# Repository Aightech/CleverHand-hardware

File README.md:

# CleverHand — Hardware

This repository contains the **hardware implementation** of the CleverHand platform.

CleverHand is an open-source, modular **Human–Machine Interface (HMI) platform** designed for
research, education, and rapid prototyping in neurotechnology, robotics, and human–robot interaction.

The hardware repository provides:

* modular PCB designs (KiCad),
* mechanical integration assets,
* manufacturing outputs,
* and per-module documentation and quality metadata.

> This repository focuses **only on hardware**.
> Firmware, software, tools, and platform-level documentation live in sibling repositories.

---

## Position in the CleverHand platform

CleverHand is structured as a **hardware / firmware / software stack**:

* **Hardware** (this repo)
  Modular, chainable PCBs for sensing, actuation, and interfacing with the human body.

* **Firmware**
  Low-level drivers, bus control, synchronization, and data transport.

* **Software & SDKs**
  Host interfaces (GUI, Python, C++, LSL, ROS, etc.).

This separation allows:

* independent evolution of hardware and software,
* reproducible research setups,
* and multiple integration paths (DIY, PCBA, pre-assembled).

---

## Intended use & scope

CleverHand hardware is designed for:

* research experiments,
* educational use,
* prototyping of assistive and interactive systems.

It is **not**:

* a medical device,
* a certified clinical system,
* a consumer product.

All designs are provided **as-is**, with readiness and quality explicitly documented per module.

---

## Design goals & constraints

| Constraint          | Status | Notes                        |
| ------------------- | :----: | ---------------------------- |
| Wearable            |   ⚒️   | Wireless support in progress |
| ≥16 channels        |    ✅   | Up to 256 channels (32 × 8)  |
| ≥2 kHz bandwidth    |    ✅   | Up to 2.5 kHz                |
| ≥16-bit resolution  |    ✅   | Up to 24-bit                 |
| Bipolar / monopolar |    ✅   | Module-dependent             |
| Modular             |    ✅   | 1–32 modules per bus         |
| Affordable          |    ✅   | ~£10–£30 per module          |
| Open-source         |    ✅   | Hardware, firmware, software |

---

## Hardware architecture overview

The hardware platform is built around a **chainable modular architecture**.

Each CleverHand system is composed of:

* a **controller** (host interface and timing),
* one **communication module** (bus arbitration),
* one or more **HMI modules**, assembled from submodules.

### Submodule types

HMI nodes are built by stacking standardized submodules:

* **Communication submodule**
  Address decoding, bus routing, chip-select handling.

* **Sensor submodule**
  Biosignal or motion acquisition (EMG, IMU, etc.).

* **Feedback submodule**
  User feedback (vibration, electrotactile stimulation, LEDs).

* **Interface submodule**
  Physical interface to the body (dry electrodes, jack, flex PCB).

This structure allows:

* rapid reconfiguration,
* high channel density,
* reuse of validated building blocks.

---

## Module catalog (hardware)

> The table below lists **implemented hardware designs**.
> Readiness (prototype / reference) and quality status are tracked via
> `description.yaml`, QC artifacts, and the generated catalog — not inferred from this table.

| Module                  | Description                            | Image                                                                      | Documentation                                            |
| ----------------------- | -------------------------------------- | -------------------------------------------------------------------------- | -------------------------------------------------------- |
| Communication (COM_MOD) | Bus communication and address decoding |                     | [README](pcb/hmi/communication/COM_MOD/README.md)            |
| EMG ADS1293             | 5-channel EMG acquisition              |  | [README](pcb/hmi/submodule/sensor/EMG_DAQ_ADS1293/README.md) |
| EMG ADS1298             | 8-channel EMG acquisition              |  | [README](pcb/hmi/submodule/sensor/EMG_DAQ_ADS1298/README.md) |
| EMG INA331              | Single-channel EMG + IMU               |            | [README](pcb/hmi/submodule/sensor/EMG_INA331/README.md)      |
| FES AO4882              | Electrotactile stimulation             |          | [README](pcb/hmi/submodule/feedback/FES_AO4882/README.md)    |
| IMU ICM-20948           | 9-axis IMU                             |        | [README](pcb/hmi/submodule/sensor/IMU_ICM20948/README.md)    |
| Dry electrodes (16ch)   | Rigid dry electrode interface          |             | [README](pcb/hmi/interface/DRY_ELEC_16CH/README.md)          |

---

## Bus architecture

CleverHand uses a **shared bus architecture** combining:

* a 5-bit address bus,
* SPI for high-rate data transfer,
* I²C for identification and configuration.

Each communication module:

* monitors the address bus,
* activates the chip-select of the targeted submodule,
* routes SPI transactions accordingly.

The full line list, connector pinout, enumeration protocol and the planned v3
changes (separable bus board, per-node I²C bridge) are specified in
**[docs/bus/README.md](docs/bus/README.md)**; the 3×10 soldered stack field that
links bus board, controller/communication module and submodules inside a node is
in **[docs/bus/interfaces.md](docs/bus/interfaces.md)**.

---

## Addressing & initialization

Module addressing is determined during an initialization phase based on
**physical position in the chain**.

Modules carry no hard-coded identity: the *n*-th node in the chain receives
address *n*, so identical modules can be placed anywhere.

Current status:

* deterministic, position-based addressing: **implemented** ([protocol](docs/bus/README.md#4-enumeration-position-based-addressing))
* re-enumeration without power cycle: **planned** (v3)
* dynamic hot-plugging: **not supported**

---

## Evaluation, QC & readiness

Hardware quality and maturity are **explicitly tracked**, not implied.

For each module:

* readiness level is declared in `description.yaml`,
* QC profiles and reports live in the module’s `qc/` folder,
* catalog readiness is generated automatically.

Only **REFERENCE-level modules** are considered stable and suitable
for external reuse without direct support.

---

## Repository structure

This repository contains the hardware designs and supporting assets for the CleverHand platform.

```
├── docs
│   ├── bus             # bus & protocol specification
│   ├── datasheet
│   ├── img
│   ├── initialisation
│   └── plots
├── LICENSE
├── pcb
│   ├── config_file
│   ├── controller
│   ├── hmi
│   └── tool
├── README.md
└── scripts
```

Each top-level directory has a clear, non-overlapping responsibility, described below.

---

## Relation to other repositories

* Firmware: see top-level CleverHand firmware repository
* Software / SDKs: see CleverHand interface repository
* Platform roadmap and policies: see top-level CleverHand README

---

## Status

The CleverHand hardware platform is **actively evolving**.

Some modules are experimental; others are approaching reference quality.
Authoritative status is always given by:

* module metadata,
* QC artifacts,
* and the generated catalog.

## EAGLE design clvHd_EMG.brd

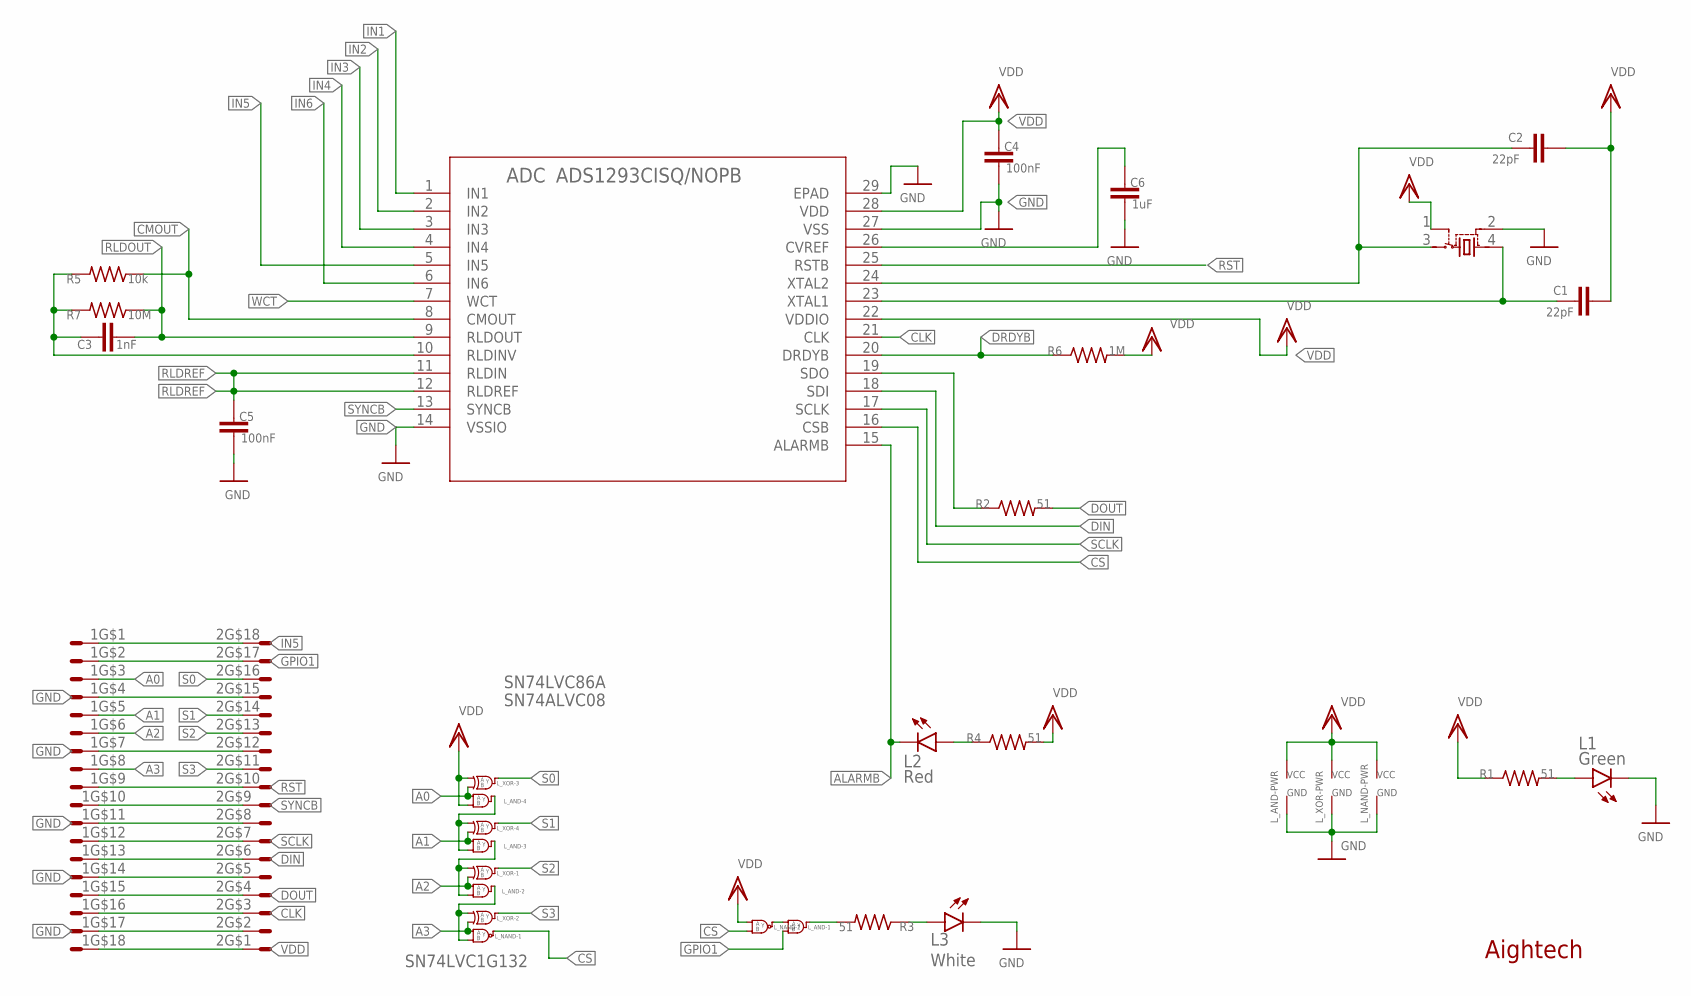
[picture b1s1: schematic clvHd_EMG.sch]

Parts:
1, 2: X05C2018TZ
ADC: ADS1293CISQ/NOPB; RSG28_3P6X3P6_TEX
C1, C2: 22pF; C0402
C3: 1nF; C0402
C4, C5: 100nF; C0402
C6: 1uF; C0402
L1: Green; CHIP-LED0603
L2: Red; CHIP-LED0603
L3: White; CHIP-LED0603
L_AND: SN74ALVC08; VQFN-14-CUSTOM
L_NAND: SN74AUP2G00; VSSOP
L_XOR: SN74LVC86; VQFN-14-CUSTOM
R1, R2, R3, R4: 51; R0402
R5: 10k; R0402
R6: 1M; R0402
R7: 10M; R0402
TAL: C387328; SMD-3225_4P

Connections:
A0: 1.3, L_AND.12 (A), L_XOR.10 (B)
A1: 1.5, L_AND.9 (A), L_XOR.13 (B)
A2: 1.6, L_AND.4 (A), L_XOR.2 (B)
A3: 1.8, L_NAND.1 (A), L_XOR.5 (B)
ALARMB: ADC.15 (ALARMB), L2.C
CLK: 1.16, 2.3, ADC.21 (CLK)
CMOUT: ADC.8 (CMOUT), R5.1
CS: ADC.16 (CSB), L_NAND.6 (B), L_NAND.7 (Y)
DIN: 1.13, 2.6, ADC.18 (SDI)
DOUT: 1.15, 2.4, R2.2
DRDYB: ADC.20 (DRDYB), R6.1
GND: 1.4, 1.7, 1.11, 1.14, 1.17, 2.2, 2.5, 2.8, 2.12, 2.15, ADC.14 (VSSIO), ADC.27 (VSS), ADC.29 (EPAD), C4.2, C5.2, C6.2, L1.C, L3.C, L_AND.7 (GND), L_AND.15 (GND), L_NAND.4 (GND), L_XOR.7 (GND), L_XOR.15 (GND), TAL.2 (GND)
GPIO1: 1.2, 2.17, L_AND.2 (B)
IN1: ADC.1 (IN1)
IN2: ADC.2 (IN2)
IN3: ADC.3 (IN3)
IN4: ADC.4 (IN4)
IN5: 1.1, 2.18, ADC.5 (IN5)
IN6: ADC.6 (IN6)
unnamed: L_AND.1 (A), L_NAND.3 (Y)
unnamed: L1.A, R1.2
unnamed: ADC.19 (SDO), R2.1
unnamed: ADC.23 (XTAL1), C1.2, TAL.4 (VDD)
unnamed: L_AND.3 (Y), R3.2
unnamed: L2.A, R4.1
unnamed: L3.A, R3.1
unnamed: ADC.24 (XTAL2), C2.2, TAL.3 (OUT)
unnamed: ADC.26 (CVREF), C6.1
unnamed: L_AND.10 (B), L_AND.11 (Y), L_XOR.12 (A)
unnamed: L_AND.5 (B), L_AND.8 (Y), L_XOR.1 (A)
unnamed: ADC.10 (RLDINV), C3.1, R5.2, R7.2
unnamed: L_AND.6 (Y), L_NAND.2 (B), L_XOR.4 (A)
RLDOUT: ADC.9 (RLDOUT), C3.2, R7.1
RLDREF: ADC.11 (RLDIN), ADC.12 (RLDREF), C5.1
RST: 1.9, 2.10, ADC.25 (RSTB)
S0: 2.16, L_XOR.8 (Y)
S1: 2.14, L_XOR.11 (Y)
S2: 2.13, L_XOR.3 (Y)
S3: 2.11, L_XOR.6 (Y)
SCLK: 1.12, 2.7, ADC.17 (SCLK)
SYNCB: 1.10, 2.9, ADC.13 (SYNCB)
VDD: 1.18, 2.1, ADC.22 (VDDIO), ADC.28 (VDD), C1.1, C2.1, C4.1, L_AND.13 (B), L_AND.14 (VCC), L_NAND.5 (A), L_NAND.8 (VCC), L_XOR.9 (A), L_XOR.14 (VCC), R1.1, R4.2, R6.2, TAL.1 (TRI)
WCT: ADC.7 (WCT)

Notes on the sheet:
Aightech
SN74LVC86A
SN74ALVC08
SN74LVC1G132

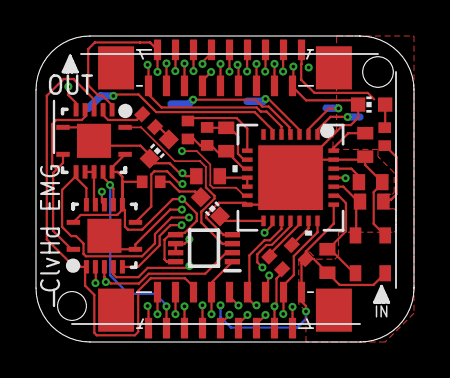
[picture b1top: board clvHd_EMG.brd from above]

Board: 4 copper layers, 21.0 x 17.0 mm, 23 parts (0 on the bottom side), 37 nets.

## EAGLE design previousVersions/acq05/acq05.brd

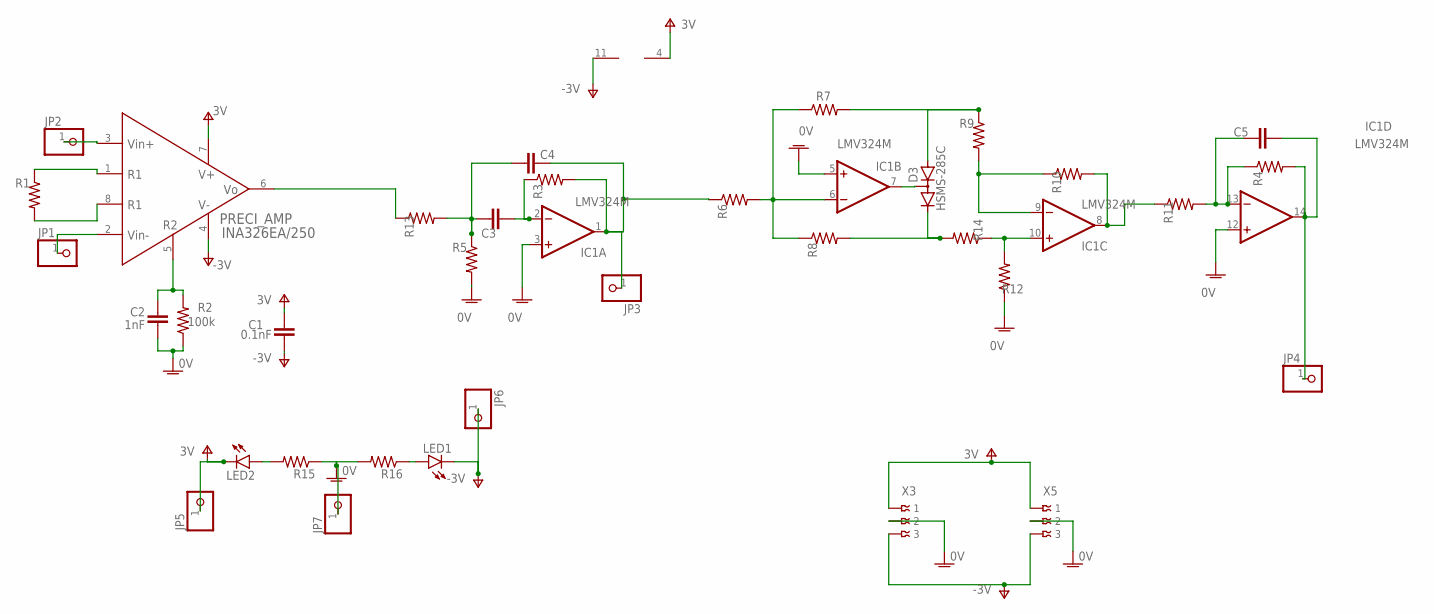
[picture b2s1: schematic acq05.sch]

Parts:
C1, C3, C4, C5: 0.1nF; C0402K
C2: 1nF; C0402K
D3: HSMS-285C; SOT323
IC1: LMV324M; SO14
JP1, JP2, JP3, JP4, JP5, JP6, JP7: PINHD-1X1; 1X01
LED1, LED2: LEDCHIP-LED0603; CHIP-LED0603
PRECI_AMP: INA326EA/250; SOP65P490X110-8N
R1, R2, R3, R4, R5, R6, R7, R8, R9, R10, R11, R12, R13, R14: 100k; R0402
R15, R16: R-US_R0402; R0402
X3, X5: 009176003

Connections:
GNDA: C2.1, IC1.3 (+IN), IC1.5 (+IN), IC1.12 (+IN), JP7.1, R2.1, R5.2, R12.1, R15.1, R16.2, X3.2, X5.2
INM: JP1.1, PRECI_AMP.2 (VIN-)
INP: JP2.1, PRECI_AMP.3 (VIN+)
unnamed: PRECI_AMP.1 (R1_2), R1.1
unnamed: PRECI_AMP.8 (R1), R1.2
unnamed: C2.2, PRECI_AMP.5 (R2), R2.2
unnamed: C3.1, IC1.2 (-IN), R3.1
unnamed: C3.2, C4.2, R5.1, R13.2
unnamed: C5.1, IC1.13 (-IN), R4.1, R11.2
unnamed: PRECI_AMP.6 (VO), R13.1
unnamed: IC1.6 (-IN), R6.2, R7.1, R8.1
unnamed: D3.2 (C), R8.2, R14.2
unnamed: IC1.9 (-IN), R9.2, R10.1
unnamed: D3.3 (AC), IC1.7 (OUT)
unnamed: D3.1 (A), R7.2, R9.1
unnamed: IC1.8 (OUT), R10.2, R11.1
unnamed: C5.2, IC1.14 (OUT), JP4.1, R4.2
unnamed: IC1.10 (+IN), R12.2, R14.1
unnamed: C4.1, IC1.1 (OUT), JP3.1, R3.2, R6.1
unnamed: LED2.A, R15.2
unnamed: LED1.A, R16.1
V+: C1.1, IC1.4 (V+), JP5.1, LED2.C, PRECI_AMP.7 (V+), X3.1, X5.1
V-: C1.2, IC1.11 (V-), JP6.1, LED1.C, PRECI_AMP.4 (V-), X3.3, X5.3

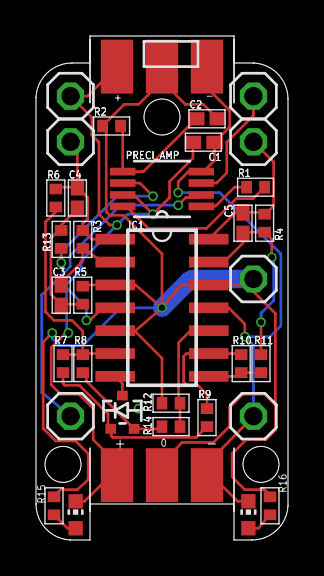
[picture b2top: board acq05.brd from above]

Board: 2 copper layers, 14.0 x 28.0 mm, 35 parts (0 on the bottom side), 23 nets.

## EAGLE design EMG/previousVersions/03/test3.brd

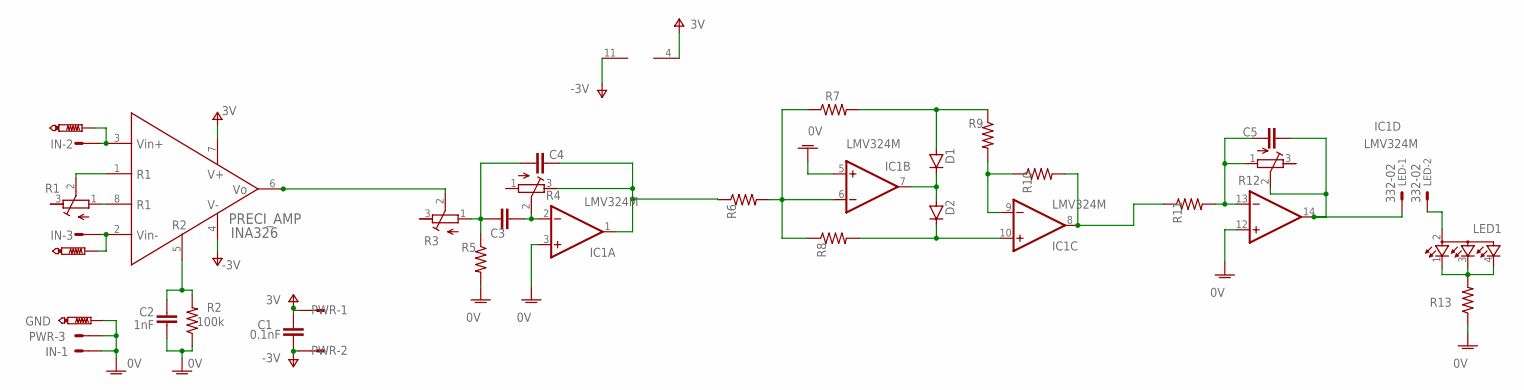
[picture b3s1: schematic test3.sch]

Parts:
C1, C3, C4, C5: 0.1nF; C0603
C2: 1nF; C0603
D1, D2: D-SOD-80; SOD80
GND: PTR1PAD1-13; P1-13
IC1: LMV324M; SO14
IN: MT6-3
IN+: PTR1PAD1-13; P1-13
IN-: PTR1PAD1-13; P1-13
LED: 332-02
LED1: TOPLED-3; P-LCC-4-3
PRECI_AMP: INA326; SOP65P490X110-8N
PWR: MT6-3
R1, R3, R4, R12: R-TRIMM4G/J; RTRIM4G/J
R2, R5, R6, R7, R8, R9, R10, R11, R13: 100k; R0603

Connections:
GNDA: C2.1, GND.TP, IC1.3 (+IN), IC1.5 (+IN), IC1.12 (+IN), IN.1, PWR.3, R2.1, R5.2, R13.1
unnamed: PRECI_AMP.8 (R1), R1.1 (A)
unnamed: PRECI_AMP.1 (R1_2), R1.2 (S)
unnamed: IN.2, IN+.TP, PRECI_AMP.3 (VIN+)
unnamed: C2.2, PRECI_AMP.5 (R2), R2.2
unnamed: IN.3, IN-.TP, PRECI_AMP.2 (VIN-)
unnamed: C3.1, IC1.2 (-IN), R4.2 (S)
unnamed: C3.2, C4.2, R3.1 (A), R5.1
unnamed: C5.1, IC1.13 (-IN), R11.2, R12.1 (A)
unnamed: PRECI_AMP.6 (VO), R3.2 (S)
unnamed: IC1.6 (-IN), R6.2, R7.1, R8.1
unnamed: D2.1 (C), IC1.10 (+IN), R8.2
unnamed: IC1.9 (-IN), R9.2, R10.1
unnamed: D1.1 (C), D2.2 (A), IC1.7 (OUT)
unnamed: D1.2 (A), R7.2, R9.1
unnamed: IC1.8 (OUT), R10.2, R11.1
unnamed: C5.2, IC1.14 (OUT), LED.1, R12.2 (S)
unnamed: LED1.1 (CRED), LED1.3 (CBLUE), LED1.4 (CGREEN), R13.2
unnamed: LED.2, LED1.2 (A2)
unnamed: C4.1, IC1.1 (OUT), R4.3 (E), R6.1
V+: C1.1, IC1.4 (V+), PRECI_AMP.7 (V+), PWR.1
V-: C1.2, IC1.11 (V-), PRECI_AMP.4 (V-), PWR.2

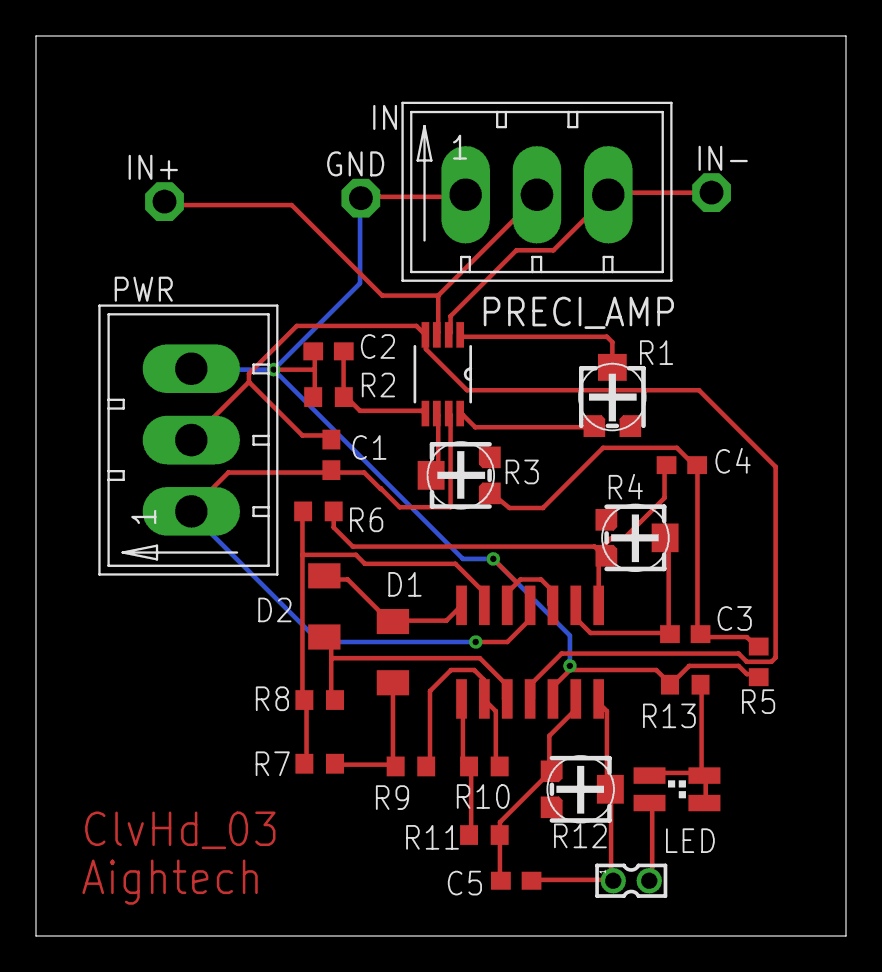
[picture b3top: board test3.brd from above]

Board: 2 copper layers, 45.0 x 50.0 mm, 29 parts (0 on the bottom side), 22 nets.

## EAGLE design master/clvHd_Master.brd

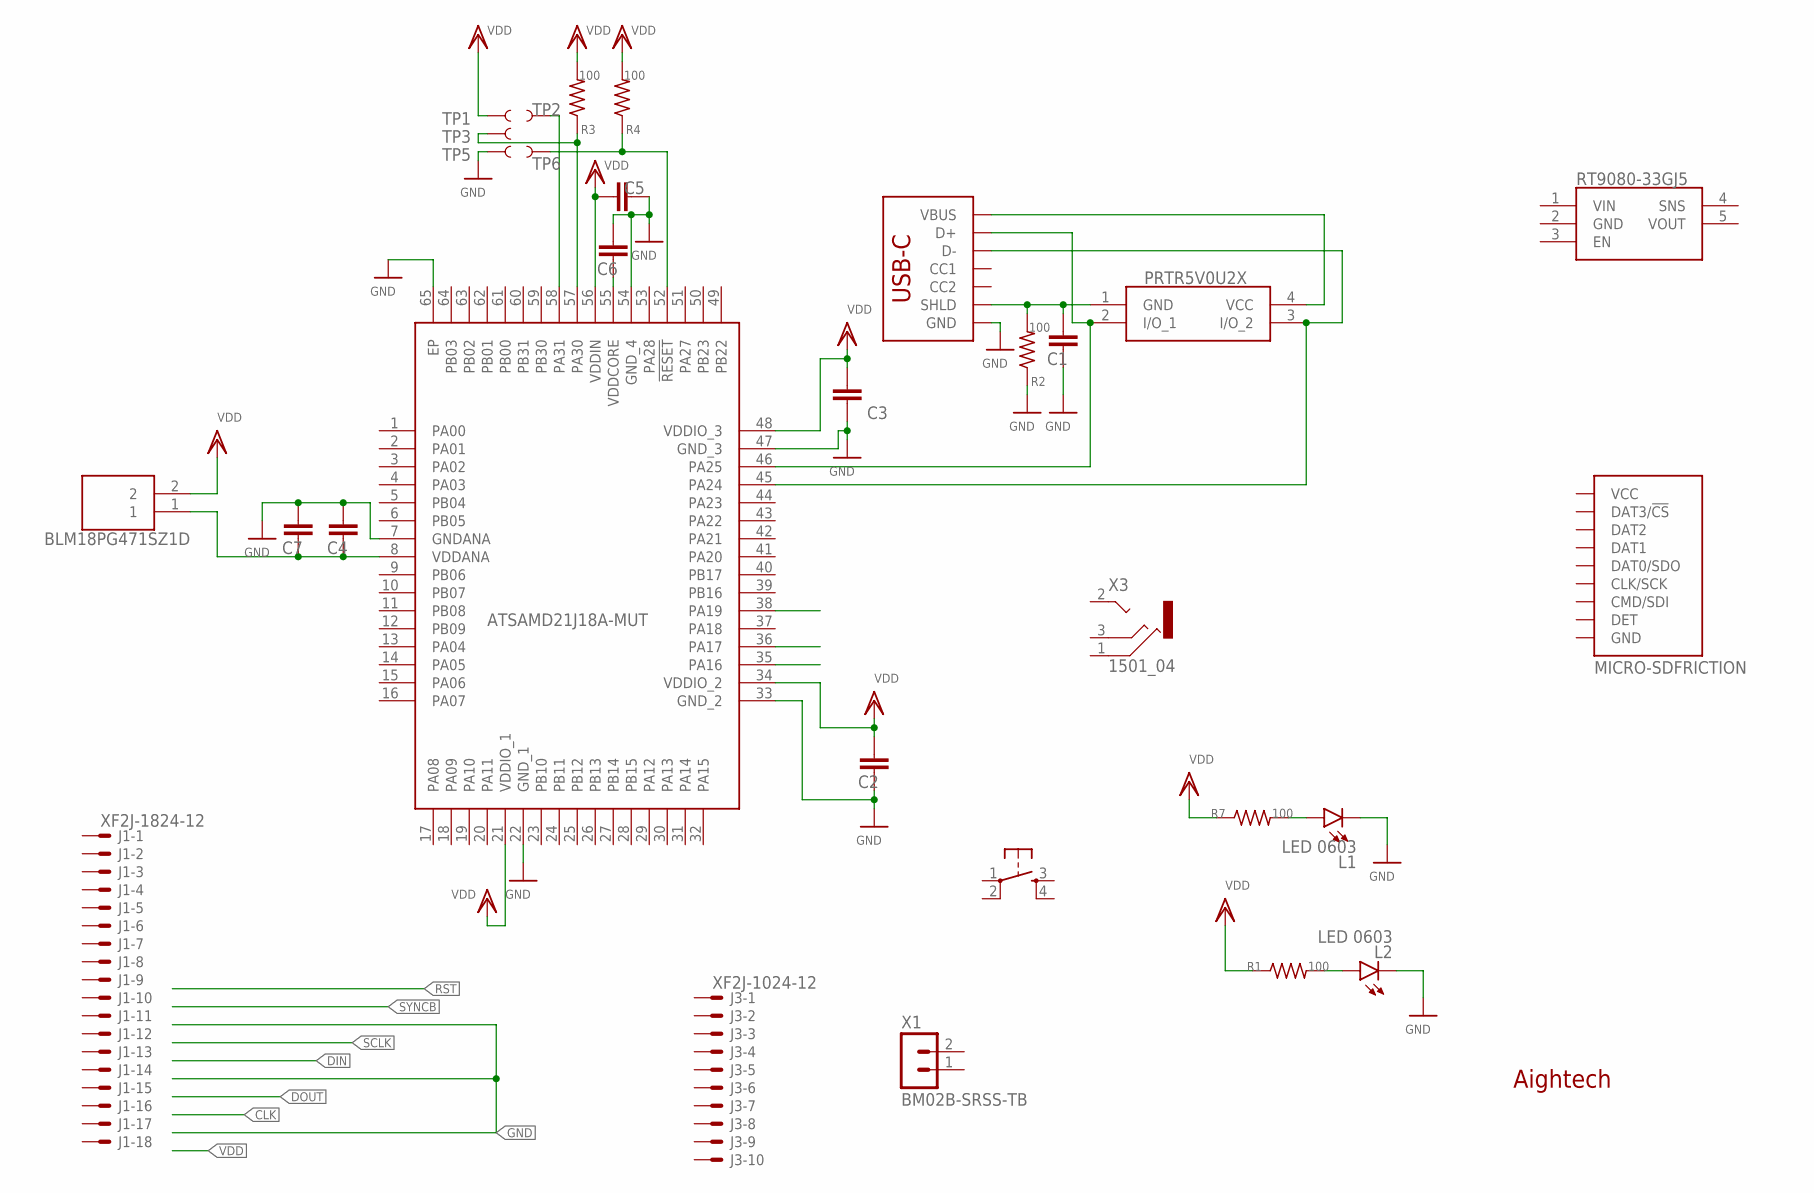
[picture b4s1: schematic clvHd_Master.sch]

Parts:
C1, C2, C3, C4, C5, C6, C7: C-EUC0402; C0402
D1: PRTR5V0U2X
FL1: BLM18PG471SZ1D; BLM18AG102BH1D
IC1: ATSAMD21J18A-MUT; QFN50P900X900X100-65N
IC2: RT9080-33GJ5; SOT94P280X100-5N
J1: XF2J-1824-12
J2: USB_C_2-LAYER_PADS; USB-C-16P-2LAYER-PADS
J3: XF2J-1024-12
J4: MICRO-SDFRICTION; MICROSD_TINY
L1, L2: LED 0603; CHIP-LED0603
R1, R2, R3, R4, R7: 100; R0402
S2: TAC_SWITCHSMD; TACTILE-SWITCH-SMD
TP1, TP2, TP3, TP5, TP6: TEST-POINT3; PAD.03X.03
X1: BM02B-SRSS-TB
X3: 1501_04; 1501_05

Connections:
GND: C1.2, C2.2, C3.2, C4.1, C5.1, C6.1, C7.1, IC1.7 (GNDANA), IC1.22 (GND_1), IC1.33 (GND_2), IC1.47 (GND_3), IC1.54 (GND_4), IC1.65 (EP), J2.GND, J2.GND2 (GND), L1.C, L2.C, R2.1, TP5.1
unnamed: L2.A, R1.2
unnamed: L1.A, R7.2
unnamed: C1.1, D1.1 (GND), J2.SHLD1 (SHLD), J2.SHLD2 (SHLD), J2.SHLD3 (SHLD), J2.SHLD4 (SHLD), R2.2
unnamed: D1.4 (VCC), J2.VBUS1 (VBUS), J2.VBUS2 (VBUS)
unnamed: D1.2 (I/O_1), IC1.46 (PA25), J2.A6 (D+), J2.B6 (D+)
unnamed: D1.3 (I/O_2), IC1.45 (PA24), J2.A7 (D-), J2.B7 (D-)
unnamed: C6.2, IC1.55 (VDDCORE)
unnamed: C4.2, C7.2, FL1.1, IC1.8 (VDDANA)
unnamed: IC1.52 (!RESET), R4.1, TP6.1
unnamed: IC1.58 (PA31), TP2.1
unnamed: IC1.57 (PA30), R3.1, TP3.1
VDD: C2.1, C3.1, C5.2, FL1.2, IC1.21 (VDDIO_1), IC1.34 (VDDIO_2), IC1.48 (VDDIO_3), IC1.56 (VDDIN), R1.1, R3.2, R4.2, R7.1, TP1.1

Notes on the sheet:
Aightech

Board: 4 copper layers, 30 parts (6 on the bottom side), 13 nets, no tracks yet.

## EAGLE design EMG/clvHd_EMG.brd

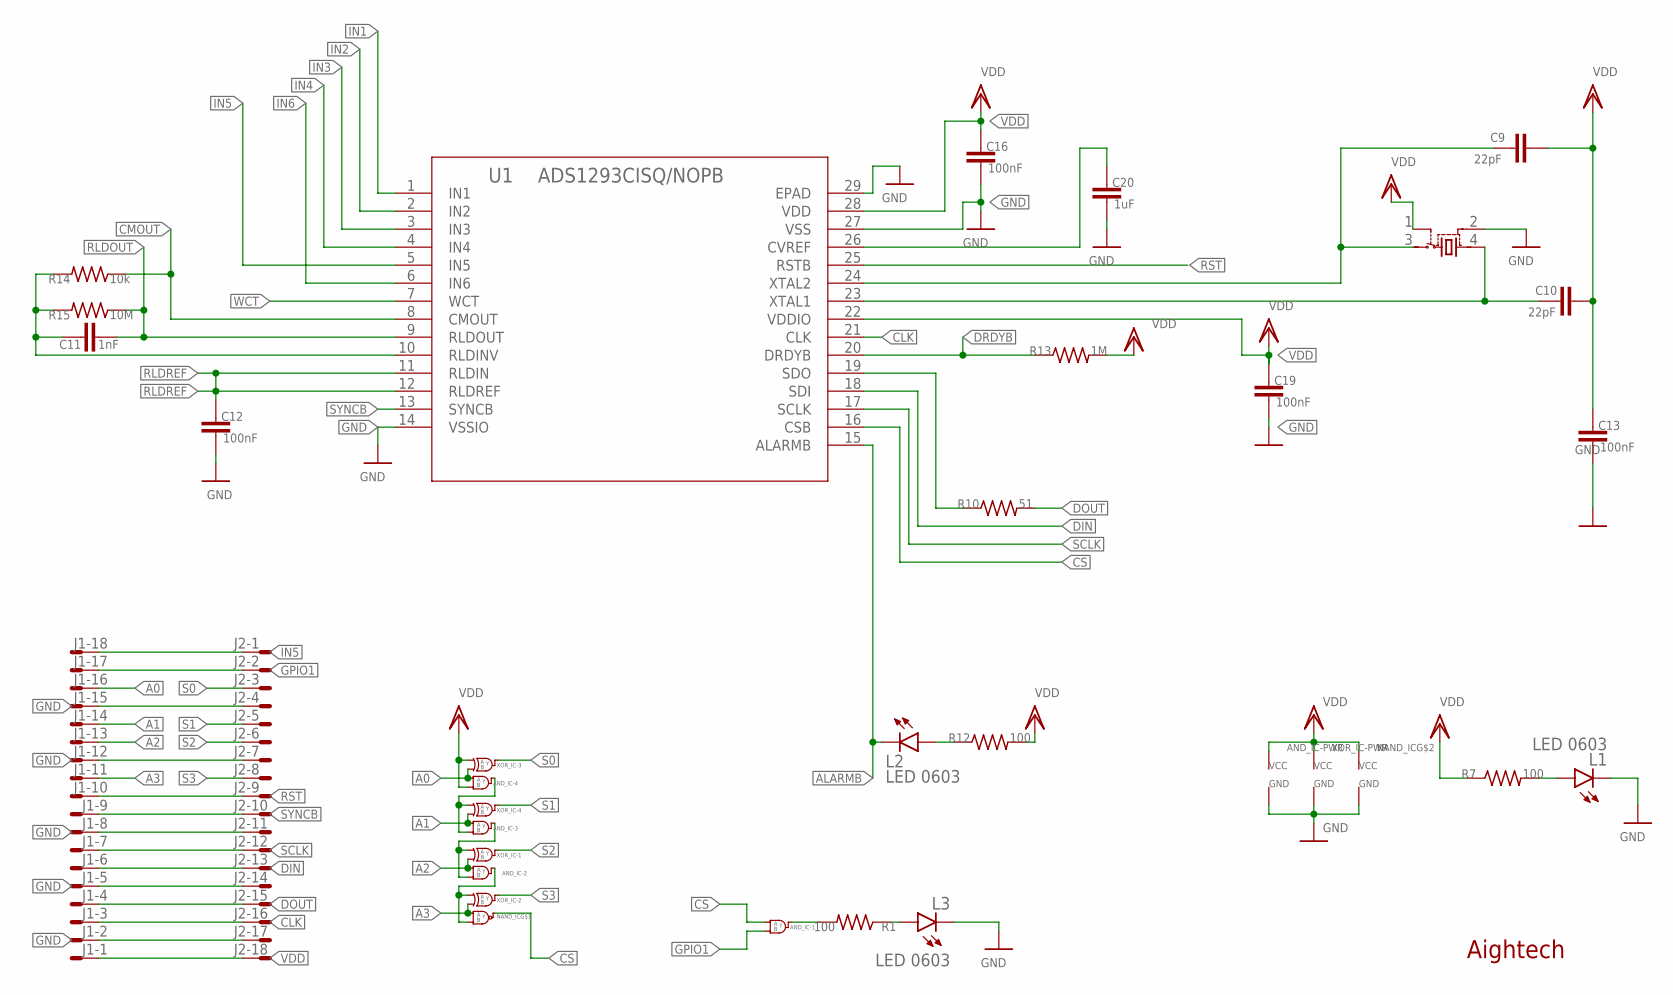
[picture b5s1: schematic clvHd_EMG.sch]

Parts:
AND_IC: SN74ALVC08LARGE; SN74LVC86ARGYR
C9, C10: 22pF; C0402
C11: 1nF; C0402
C12, C13, C16, C19: 100nF; C0402
C20: 1uF; C0402
J1, J2: XF2J-1824-12
L1, L2, L3: LED 0603; CHIP-LED0603
NAND_IC: SN74LVC1G132DCKT; SOT65P210X110-5N
R1, R7, R12: 100; R0402
R10: 51; R0402
R13: 1M; R0402
R14: 10k; R0402
R15: 10M; R0402
U1: ADS1293CISQ/NOPB; RSG28_3P6X3P6_TEX
U$1: C387328; SMD-3225_4P
XOR_IC: SN74LVC86A; SN74LVC86ARGYR

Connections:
A0: AND_IC.12 (A), J1.16 (MS), XOR_IC.10 (B)
A1: AND_IC.9 (A), J1.14 (MS), XOR_IC.13 (B)
A2: AND_IC.4 (A), J1.13 (MS), XOR_IC.2 (B)
A3: J1.11 (MS), NAND_IC.1 (A), XOR_IC.5 (B)
ALARMB: L2.C, U1.15 (ALARMB)
CLK: J1.3 (MS), J2.16 (MS), U1.21 (CLK)
CMOUT: R14.1, U1.8 (CMOUT)
CS: AND_IC.1 (A), NAND_IC.4 (Y), U1.16 (CSB)
DIN: J1.6 (MS), J2.13 (MS), U1.18 (SDI)
DOUT: J1.4 (MS), J2.15 (MS), R10.2
DRDYB: R13.1, U1.20 (DRDYB)
GND: AND_IC.7 (GND), AND_IC.15 (GND), C12.2, C13.2, C16.2, C19.2, C20.2, J1.2 (MS), J1.5 (MS), J1.8 (MS), J1.12 (MS), J1.15 (MS), J2.4 (MS), J2.7 (MS), J2.11 (MS), J2.14 (MS), J2.17 (MS), L1.C, L3.C, NAND_IC.3 (GND), U1.14 (VSSIO), U1.27 (VSS), U1.29 (EPAD), U$1.2 (GND), XOR_IC.7 (GND), XOR_IC.15 (GND)
GPIO1: AND_IC.2 (B), J1.17 (MS), J2.2 (MS)
IN1: U1.1 (IN1)
IN2: U1.2 (IN2)
IN3: U1.3 (IN3)
IN4: U1.4 (IN4)
IN5: J1.18 (MS), J2.1 (MSV), U1.5 (IN5)
IN6: U1.6 (IN6)
unnamed: L1.A, R7.2
unnamed: R10.1, U1.19 (SDO)
unnamed: C10.2, U1.23 (XTAL1), U$1.4 (VDD)
unnamed: AND_IC.3 (Y), R1.2
unnamed: L2.A, R12.1
unnamed: L3.A, R1.1
unnamed: C9.2, U1.24 (XTAL2), U$1.3 (OUT)
unnamed: C20.1, U1.26 (CVREF)
unnamed: AND_IC.10 (B), AND_IC.11 (Y), XOR_IC.12 (A)
unnamed: AND_IC.5 (B), AND_IC.8 (Y), XOR_IC.1 (A)
unnamed: C11.1, R14.2, R15.2, U1.10 (RLDINV)
unnamed: AND_IC.6 (Y), NAND_IC.2 (B), XOR_IC.4 (A)
RLDOUT: C11.2, R15.1, U1.9 (RLDOUT)
RLDREF: C12.1, U1.11 (RLDIN), U1.12 (RLDREF)
RST: J1.10 (MS), J2.9 (MS), U1.25 (RSTB)
S0: J2.3 (MS), XOR_IC.8 (Y)
S1: J2.5 (MS), XOR_IC.11 (Y)
S2: J2.6 (MS), XOR_IC.3 (Y)
S3: J2.8 (MS), XOR_IC.6 (Y)
SCLK: J1.7 (MS), J2.12 (MS), U1.17 (SCLK)
SYNCB: J1.9 (MS), J2.10 (MS), U1.13 (SYNCB)
VDD: AND_IC.13 (B), AND_IC.14 (VCC), C9.1, C10.1, C13.1, C16.1, C19.1, J1.1 (MSV), J2.18 (MS), NAND_IC.5 (VCC), R7.1, R12.2, R13.2, U1.22 (VDDIO), U1.28 (VDD), U$1.1 (TRI), XOR_IC.9 (A), XOR_IC.14 (VCC)
WCT: U1.7 (WCT)

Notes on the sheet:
Aightech

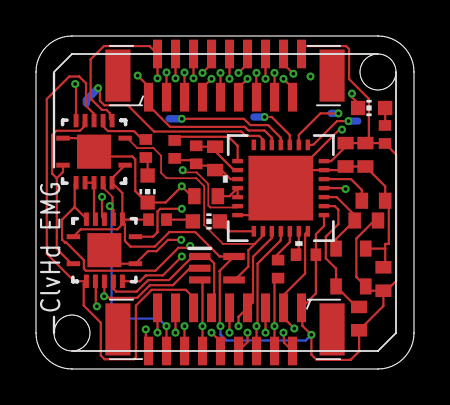
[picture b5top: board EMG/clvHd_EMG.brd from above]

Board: 4 copper layers, 21.0 x 18.5 mm, 25 parts (0 on the bottom side), 36 nets.

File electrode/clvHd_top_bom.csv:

Comment,Designator,Footprint,LCSC Part #
1M,R11 R13,R0402,
1nF,C11,C0402,
1uF,C20,C0402,
10M,R15,R0402,
10k,R14,R0402,
22pF,C9 C10,C0402,
51,R10,R0402,
100,R7 R12,R0402,
100nF,C12 C13 C16 C19,C0402,
ADS1293CISQ/NOPB,U1,RSG28_3P6X3P6_TEX,
BM02B-SRSS-TB,X1,BM02B-SRSS-TB,
BM07B-SRSS-TB,X2 X3,BM07B-SRSS-TB,
C387328 ,U$1,SMD-3225_4P,
LED 0603,L1 L2,CHIP-LED0603,
TAC_SWITCHSMD,S1,TACTILE-SWITCH-SMD,
TEST-POINT3,TP1 TP2 TP11 TP12 TP19 TP20,PAD.03X.03,

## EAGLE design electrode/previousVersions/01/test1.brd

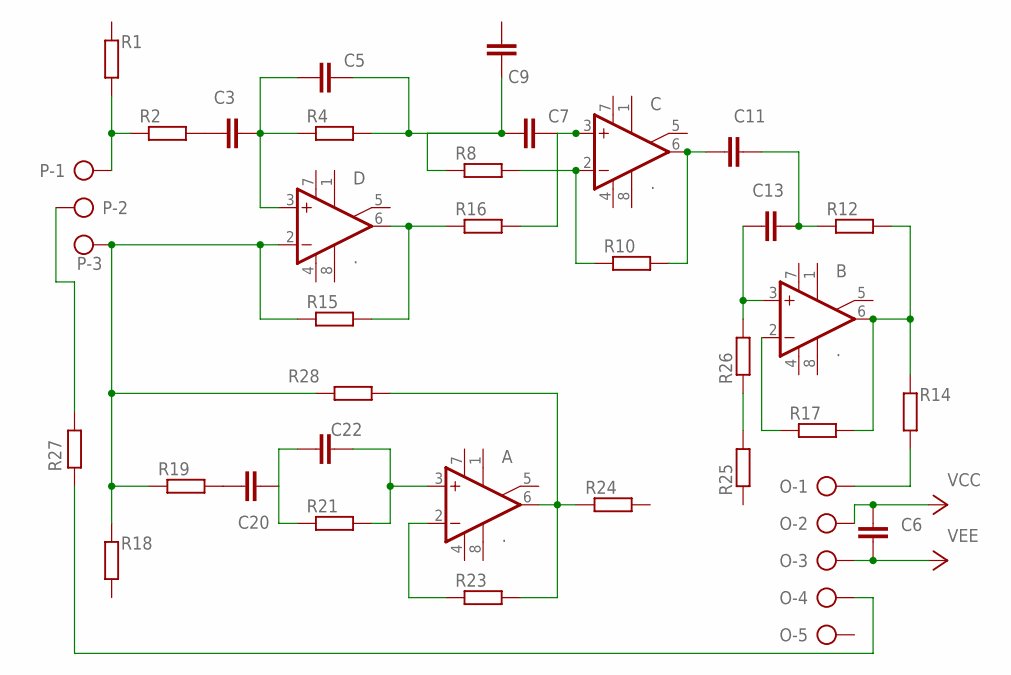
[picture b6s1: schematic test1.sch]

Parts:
A: .; SO08
B: .; SO08
C: .; SO08
C3, C5, C6, C7, C9, C11, C13, C20, C22: C-EUC1210; C1210
D: .; SO08
O: AK500/5-H
P: AK500/3-H
R1, R2, R4, R8, R10, R12, R14, R15, R16, R17, R18, R19, R21, R23, R24, R25, R26, R27, R28: RR1206; R1206

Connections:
unnamed: P.1, R1.2, R2.1
unnamed: C3.1, R2.2
unnamed: C3.2, C5.1, D.3 (+IN), R4.1
unnamed: C11.2, C13.2, R12.1
unnamed: O.1, R14.1
unnamed: C.3 (+IN), C7.2, R16.2
unnamed: C5.2, C7.1, C9.1, R4.2, R8.1
unnamed: C.2 (-IN), R8.2, R10.1
unnamed: C.6 (OUT), C11.1, R10.2
unnamed: B.3 (+IN), C13.1, R26.2
unnamed: B.6 (OUT), R12.2, R14.2, R17.2
unnamed: B.2 (-IN), R17.1
unnamed: D.6 (OUT), R15.2, R16.1
unnamed: D.2 (-IN), P.3, R15.1, R18.2, R19.1, R28.1
unnamed: C20.1, R19.2
unnamed: C20.2, C22.1, R21.1
unnamed: A.3 (+IN), C22.2, R21.2
unnamed: R25.2, R26.1
unnamed: A.2 (-IN), R23.1
unnamed: A.6 (OUT), R23.2, R24.1, R28.2
unnamed: P.2, R27.1
unnamed: O.4, R27.2
V+: A.7 (V+), B.7 (V+), C.7 (V+), D.7 (V+)
V-: A.4 (V-), B.4 (V-), C.4 (V-), D.4 (V-)
VCC: C6.1, C6.2, O.2, O.3

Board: 2 copper layers, 34 parts (0 on the bottom side), 25 nets, no tracks yet.

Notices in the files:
parts and their libraries:
SparkFun-Aesthetics: Licensing: Creative Commons ShareAlike 4.0 International - https://creativecommons.org/licenses/by-sa/4.0
